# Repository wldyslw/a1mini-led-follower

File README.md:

# A1 mini LED strip follower

A small add-on board that drives an external 24 V LED strip on the Bambu Lab A1 mini.
The strip turns on and off together with the printer's built-in light, so you control it
from the printer screen, Bambu Studio or Bambu Handy.
 
## How it works
 
- **Power:** 24 V from the printer's spare AMS port, through a resettable fuse, TVS clamp and reverse-polarity diode.
- **Sense:** two wires soldered to the legs of one built-in LED in the camera module drive a PC817 optocoupler, keeping the printer's LED circuit isolated from the 24 V side.
- **Switch:** the optocoupler turns on a MOSFET that switches the strip's negative wire. The strip is off at power-up.

See KiCad sources in this repo for the full schematic.
 
## Building it
 
1. Measure the voltage across one built-in LED with the light on, then set R1 = (V − 1.2 V) / 2 mA (about 1 kΩ for 3 V).
2. Measure your strip's current and pick F1 with a hold current of about twice that, rated for at least 30 V.
3. Check the AMS cable's pinout with a multimeter. Only +24 V and GND are used; leave the data pins unconnected.
4. Solder the twisted-pair tap to one LED's legs, route it out of the camera module with strain relief, and test before closing everything up.

I designed the PCB for through-hole parts, the BOM is in the schematic. Assembled PCB should more or less fit behind the camera module access cover.
 
## ⚠️ Disclaimer
 
This modification opens the printer and solders to the camera board. It voids your warranty,
and a mistake can damage the printer. Do it at your own risk.
 
Not affiliated with or endorsed by Bambu Lab. "Bambu Lab" and "A1 mini" are trademarks of their owner
and are used here only to describe compatibility.
 
## License
 
[MIT](LICENSE)

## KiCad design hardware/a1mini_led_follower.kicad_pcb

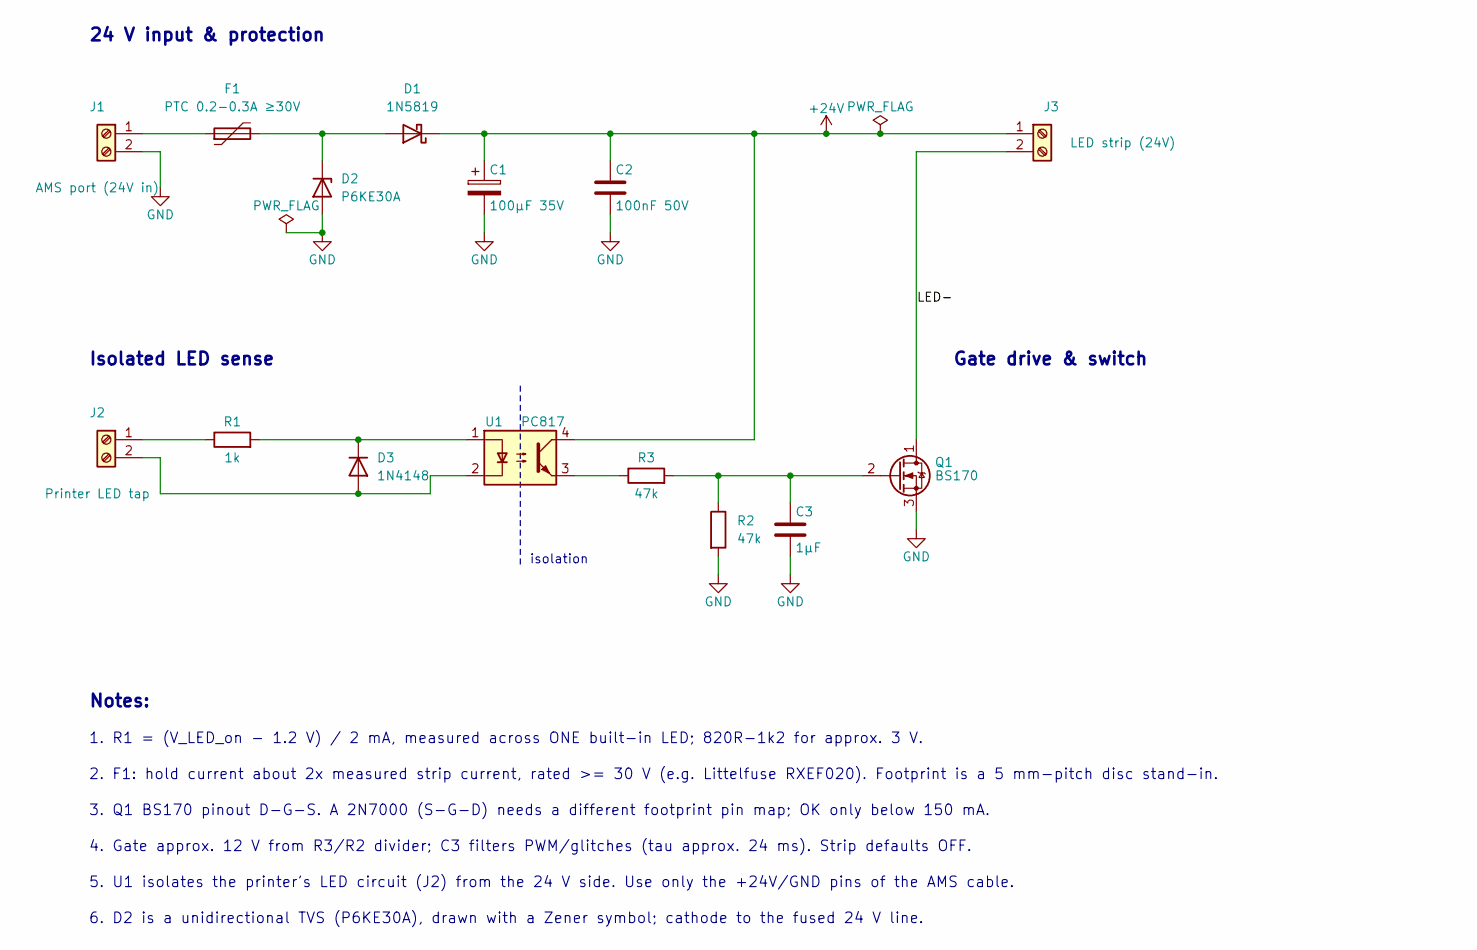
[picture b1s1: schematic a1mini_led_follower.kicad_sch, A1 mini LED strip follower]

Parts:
C1: 100µF 35V; CP_Radial_D6.3mm_P2.50mm
C2: 100nF 50V; C_Disc_D5.0mm_W2.5mm_P5.00mm
C3: 1µF; C_Disc_D5.0mm_W2.5mm_P5.00mm
D1: 1N5819; D_DO-41_SOD81_P10.16mm_Horizontal
D2: P6KE30A; D_DO-15_P10.16mm_Horizontal
D3: 1N4148; D_DO-35_SOD27_P7.62mm_Horizontal
F1: PTC 0.2-0.3A ≥30V; C_Disc_D7.5mm_W5.0mm_P5.00mm
J1: AMS port (24V in); JST_XH_B2B-XH-A_1x02_P2.50mm_Vertical
J2: Printer LED tap; JST_XH_B2B-XH-A_1x02_P2.50mm_Vertical
J3: LED strip (24V); JST_XH_B2B-XH-A_1x02_P2.50mm_Vertical
Q1: BS170; TO-92_Inline
R1: 1k; R_Axial_DIN0207_L6.3mm_D2.5mm_P10.16mm_Horizontal
R2, R3: 47k; R_Axial_DIN0207_L6.3mm_D2.5mm_P10.16mm_Horizontal
U1: PC817; DIP-4_W7.62mm

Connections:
+24V: C1.1, C2.1, D1.1 (K), J3.1, U1.4
/LED-: J3.2, Q1.1 (D)
GND: C1.2, C2.2, C3.2, D2.2 (A), J1.2, Q1.3 (S), R2.2
unnamed: D1.2 (A), D2.1 (K), F1.2
unnamed: D3.2 (A), J2.2, U1.2
unnamed: D3.1 (K), R1.2, U1.1
unnamed: F1.1, J1.1
unnamed: J2.1, R1.1
unnamed: C3.1, Q1.2 (G), R2.1, R3.2
unnamed: R3.1, U1.3

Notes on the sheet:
isolation
Gate drive & switch
Isolated LED sense
2. F1: hold current about 2x measured strip current, rated >= 30 V (e.g. Littelfuse RXEF020). Footprint is a 5 mm-pitch disc stand-in.
5. U1 isolates the printer's LED circuit (J2) from the 24 V side. Use only the +24V/GND pins of the AMS cable.
6. D2 is a unidirectional TVS (P6KE30A), drawn with a Zener symbol; cathode to the fused 24 V line.
4. Gate approx. 12 V from R3/R2 divider; C3 filters PWM/glitches (tau approx. 24 ms). Strip defaults OFF.
24 V input & protection
3. Q1 BS170 pinout D-G-S. A 2N7000 (S-G-D) needs a different footprint pin map; OK only below 150 mA.
Notes:
1. R1 = (V_LED_on - 1.2 V) / 2 mA, measured across ONE built-in LED; 820R-1k2 for approx. 3 V.

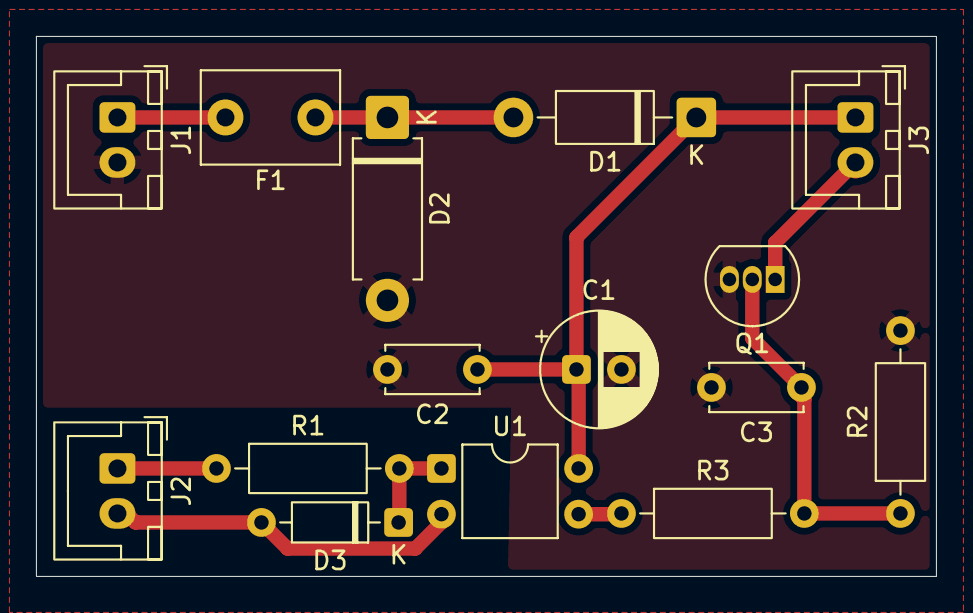
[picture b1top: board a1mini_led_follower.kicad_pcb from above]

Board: 2 copper layers, 50.0 x 30.0 mm, 15 parts (0 on the bottom side), 10 nets.
